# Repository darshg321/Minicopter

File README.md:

# Minicopter

A lightweight ESP-32 based drone capable of autonomous pathing, built for agility. Uses the GY-87 breakout board with a three-axis gyroscope + triaxial accelerometer + three-axis magnetic field + pressure. Charges a LiPo battery with USB-C and can be flashed with firmware.
Can be controlled with both pathing commands and bluetooth controls.

I made this project after getting inspiration from a different esp32 drone reel, and thought I could make that too
I've additionally always wanted to get into creating a from-scratch hardware project that includes microcontrollers and pcbs, and thought this was the perfect place to start

## Read the [JOURNAL.md](JOURNAL.md)

# BOM

| Value                               | Qty | Price (USD, approx) |
|-------------------------------------|-----|-------------|
| 10uF                                | 3   | 0.46        |
| 470pF                               | 1   | 0.4        |
| 2.2uF                               | 1   |    0.19         |
| 100nF                               | 2   |        0.14     |
| 10nF                                | 1   |         0.09    |
| 1uF                                 | 4   |          0.05   |
| SS34                                | 1   | 0.66        |
| LED                                 | 5   | 1.39        |
| 1N4148W                             | 4   | 0.77        |
| USB_C_Receptacle_USB2.0_16P         | 1   | 0.88        |
| Conn_01x02                          | 1   | 1.39        |
| Conn_01x02_Socket                   | 4   | 0.70        |
| AO3401A                             | 1   | 0.46        |
| 5.1K                                | 2   | 0.45        |
| 100K                                | 4   |     0.2        |
| 470                                 | 1   |       0.28      |
| 1.2K                                | 1   |          0.61   |
| 1K                                  | 4   |          0.2   |
| 10K                                 | 6   |            0.19 |
| SS-12D00                            | 1   | 1.39        |
| IRLML6344TRPBF                      | 4   | 1.08        |
| SPX3819M5-L-3-3                     | 1   | 0.46        |
| TP4056-42-ESOP8                     | 1   | 1.73        |
| ESP32-C3-WROOM-02                   | 1   | 3.28        |
| GY-87_Module                        | 1   | 3.00        |
| USBLC6-2P6                          | 1   | 0.46        |
| 3.7V 500mAh 902530 25C LiPo Battery | 3   | 12.68       |
| NewBeeDrone BDR Unicorn Edition Motors - 6mm Brushed Motors    | 1   | 19.99       |
| NewBeeDrone Venom V2 Super Durable Propellers     | 1   | 2.99        |
| Total (w/ shipping + tax)           |     | 138.15      |

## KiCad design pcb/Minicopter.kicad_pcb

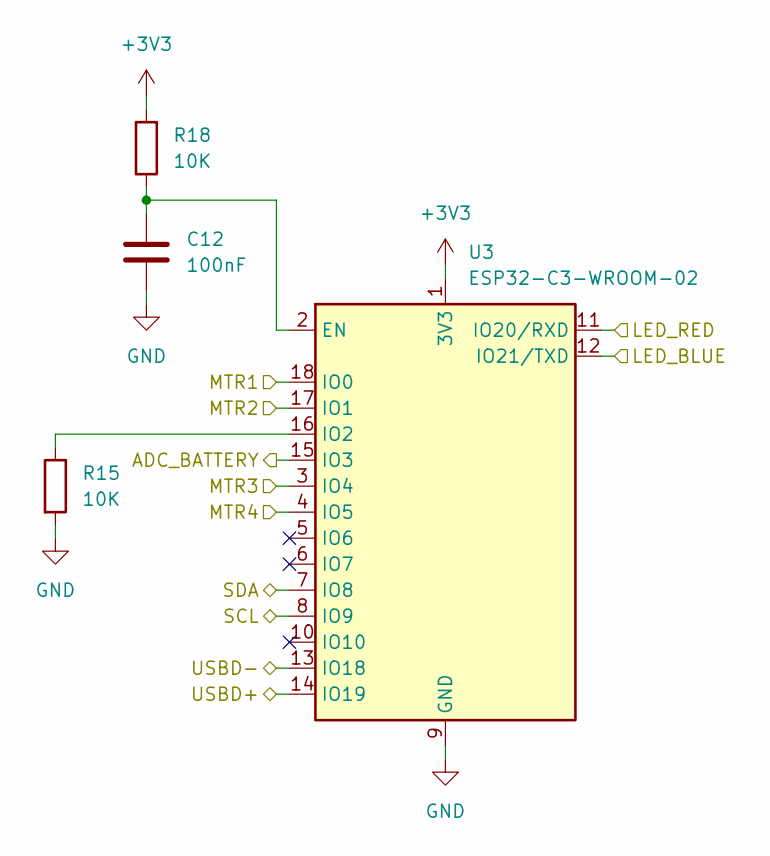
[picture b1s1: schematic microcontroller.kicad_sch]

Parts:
C12: 100nF; C_0603_1608Metric
R15, R18: 10K; R_0603_1608Metric
U3: ESP32-C3-WROOM-02

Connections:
+3V3: R18.2, U3.1 (3V3); also elsewhere on the board
/battery control/ADC_BATTERY: U3.15 (IO3); also elsewhere on the board
/microcontroller/LED_BLUE: U3.12 (IO21/TXD); also elsewhere on the board
/microcontroller/LED_RED: U3.11 (IO20/RXD); also elsewhere on the board
/microcontroller/MTR1: U3.18 (IO0); also elsewhere on the board
/microcontroller/MTR2: U3.17 (IO1); also elsewhere on the board
/microcontroller/MTR3: U3.3 (IO4); also elsewhere on the board
/microcontroller/MTR4: U3.4 (IO5); also elsewhere on the board
/microcontroller/SCL: U3.8 (IO9); also elsewhere on the board
/microcontroller/SDA: U3.7 (IO8); also elsewhere on the board
/microcontroller/USBD+: U3.14 (IO19); also elsewhere on the board
/microcontroller/USBD-: U3.13 (IO18); also elsewhere on the board
GND: C12.2, R15.2, U3.9 (GND), U3.19 (GND); also elsewhere on the board
unnamed: C12.1, R18.1, U3.2 (EN)
unnamed: R15.1, U3.16 (IO2)

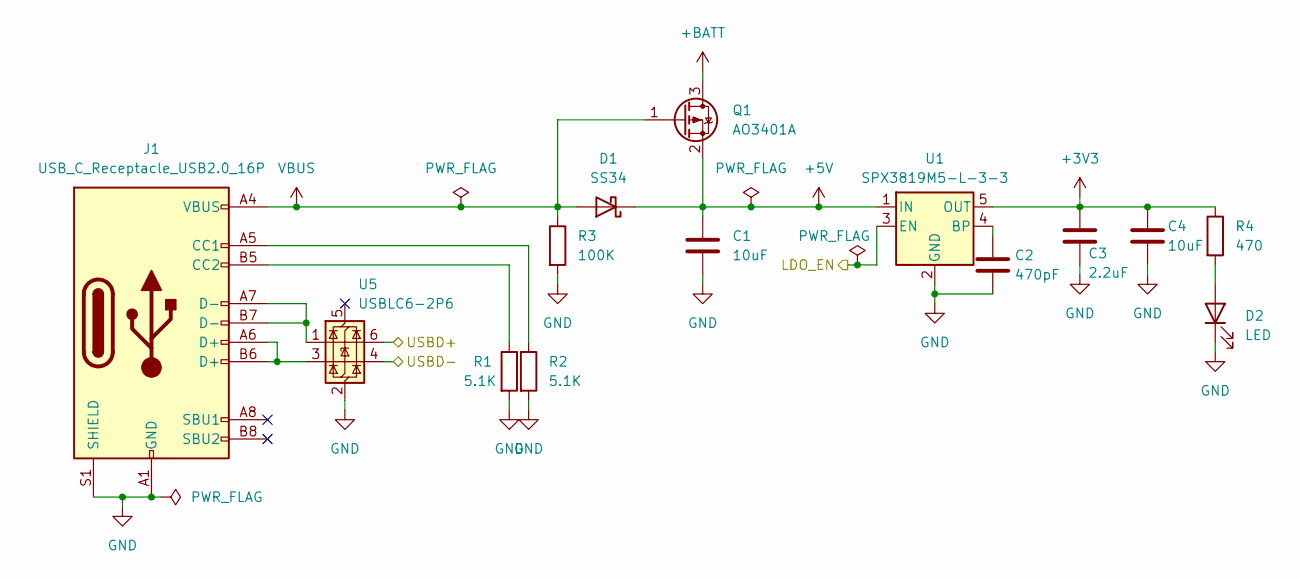
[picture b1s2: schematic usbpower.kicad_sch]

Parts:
C1, C4: 10uF; C_0603_1608Metric
C2: 470pF; C_0603_1608Metric
C3: 2.2uF; C_0603_1608Metric
D1: SS34; D_SMA
D2: LED; LED_0603_1608Metric
J1: USB_C_Receptacle_USB2.0_16P; USB_C_Receptacle_GCT_USB4085
Q1: AO3401A; SOT-23
R1, R2: 5.1K; R_0603_1608Metric
R3: 100K; R_0603_1608Metric
R4: 470; R_0603_1608Metric
U1: SPX3819M5-L-3-3; SOT-23-5
U5: USBLC6-2P6; SOT-666

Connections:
+3V3: C3.1, C4.1, R4.1, U1.5 (OUT); also elsewhere on the board
+5V: C1.1, D1.1 (K), Q1.2 (S), U1.1 (IN); also elsewhere on the board
+BATT: Q1.3 (D); also elsewhere on the board
/battery control/LDO_EN: U1.3 (EN); also elsewhere on the board
/microcontroller/USBD+: U5.6 (I/O1); also elsewhere on the board
/microcontroller/USBD-: U5.4 (I/O2); also elsewhere on the board
GND: C1.2, C2.2, C3.2, C4.2, D2.1 (K), J1.A1 (GND), J1.A12 (GND), J1.B1 (GND), J1.B12 (GND), J1.S1 (SHIELD), R1.2, R2.2, R3.2, U1.2 (GND), U5.2 (GND); also elsewhere on the board
unnamed: D2.2 (A), R4.2
unnamed: J1.A5 (CC1), R2.1
unnamed: J1.B5 (CC2), R1.1
unnamed: J1.A6 (D+), J1.B6 (D+), U5.3 (I/O2)
unnamed: J1.A7 (D-), J1.B7 (D-), U5.1 (I/O1)
unnamed: C2.1, U1.4 (BP)
VBUS: D1.2 (A), J1.A4 (VBUS), J1.A9 (VBUS), J1.B4 (VBUS), J1.B9 (VBUS), Q1.1 (G), R3.1; also elsewhere on the board

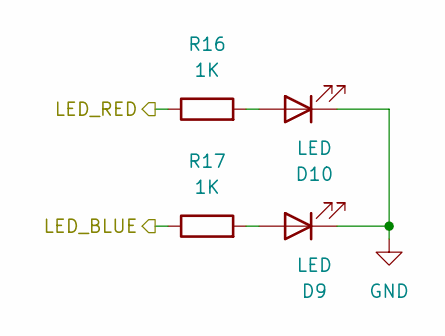
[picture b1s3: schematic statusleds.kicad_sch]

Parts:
D9, D10: LED; LED_0603_1608Metric
R16, R17: 1K; R_0603_1608Metric

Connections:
/microcontroller/LED_BLUE: R17.1; also elsewhere on the board
/microcontroller/LED_RED: R16.1; also elsewhere on the board
GND: D9.1 (K), D10.1 (K); also elsewhere on the board
unnamed: D9.2 (A), R17.2
unnamed: D10.2 (A), R16.2

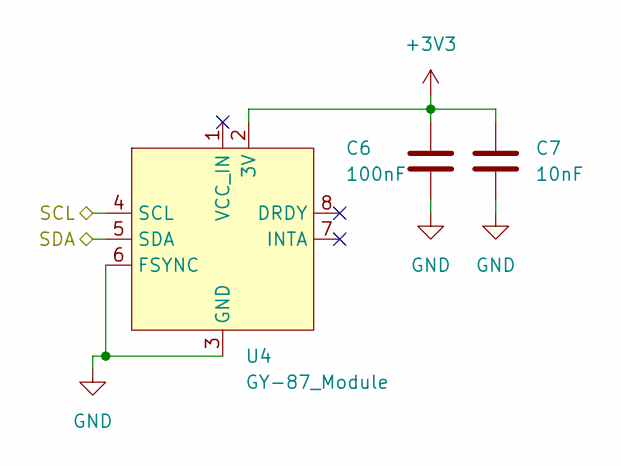
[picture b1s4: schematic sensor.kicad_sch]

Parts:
C6: 100nF; C_0603_1608Metric
C7: 10nF; C_0603_1608Metric
U4: GY-87_Module

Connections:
+3V3: C6.1, C7.1, U4.2 (3V); also elsewhere on the board
/microcontroller/SCL: U4.4 (SCL); also elsewhere on the board
/microcontroller/SDA: U4.5 (SDA); also elsewhere on the board
GND: C6.2, C7.2, U4.3 (GND), U4.6 (FSYNC); also elsewhere on the board

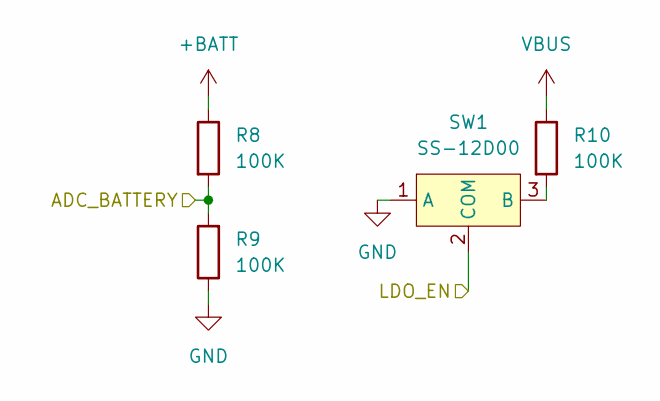
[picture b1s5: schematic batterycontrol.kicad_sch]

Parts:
R8, R9, R10: 100K; R_0603_1608Metric
SW1: SS-12D00; SS12-D00

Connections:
+BATT: R8.1; also elsewhere on the board
/battery control/ADC_BATTERY: R8.2, R9.2; also elsewhere on the board
/battery control/LDO_EN: SW1.2 (COM); also elsewhere on the board
GND: R9.1, SW1.1 (A); also elsewhere on the board
unnamed: R10.2, SW1.3 (B)
VBUS: R10.1; also elsewhere on the board

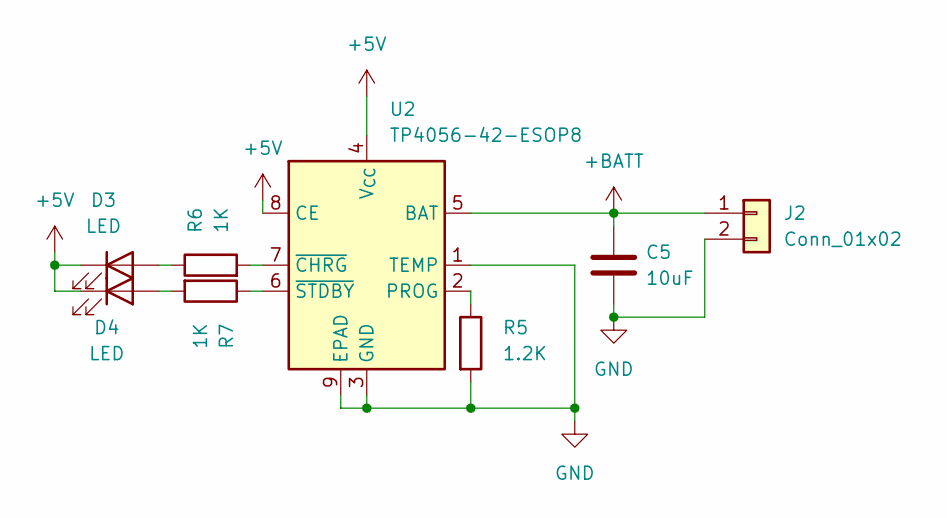
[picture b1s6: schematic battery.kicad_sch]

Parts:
C5: 10uF; C_0603_1608Metric
D3, D4: LED; LED_0603_1608Metric
J2: Conn_01x02; JST_PH_B2B-PH-SM4-TB_1x02-1MP_P2.00mm_Vertical
R5: 1.2K; R_0603_1608Metric
R6, R7: 1K; R_0603_1608Metric
U2: TP4056-42-ESOP8; SOIC-8-1EP_3.9x4.9mm_P1.27mm_EP2.41x3.3mm_ThermalVias

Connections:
+5V: D3.1 (K), D4.1 (K), U2.4 (V_{CC}), U2.8 (CE); also elsewhere on the board
+BATT: C5.1, J2.1, U2.5 (BAT); also elsewhere on the board
GND: C5.2, J2.2, R5.2, U2.1 (TEMP), U2.3 (GND), U2.9 (EPAD); also elsewhere on the board
unnamed: D3.2 (A), R6.1
unnamed: D4.2 (A), R7.2
unnamed: R5.1, U2.2 (PROG)
unnamed: R6.2, U2.7 (~CHRG)
unnamed: R7.1, U2.6 (~STDBY)

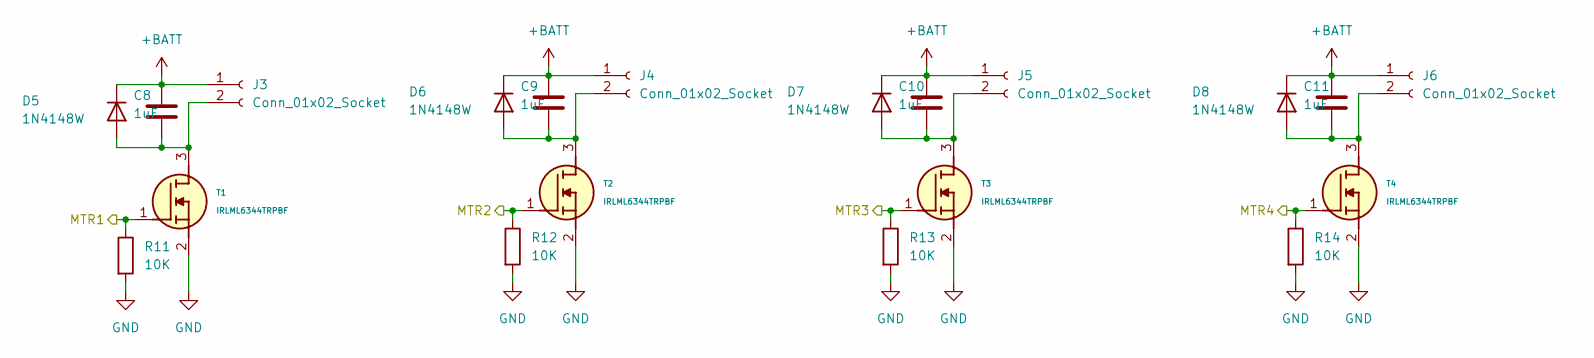
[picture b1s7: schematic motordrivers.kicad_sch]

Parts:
C8, C9, C10, C11: 1uF; C_0603_1608Metric
D5, D6, D7, D8: 1N4148W; D_SOD-123
J3, J4, J5, J6: Conn_01x02_Socket; JST_GH_BM02B-GHS-TBT_1x02-1MP_P1.25mm_Vertical
R11, R12, R13, R14: 10K; R_0603_1608Metric
T1, T2, T3, T4: IRLML6344TRPBF; MFR.Part # IRLML6344TRPBF-HXY; LCSC Part # C6285738

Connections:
+BATT: C8.1, C9.1, C10.1, C11.1, D5.1 (K), D6.1 (K), D7.1 (K), D8.1 (K), J3.1, J4.1, J5.1, J6.1; also elsewhere on the board
/microcontroller/MTR1: R11.1, T1.1 (G); also elsewhere on the board
/microcontroller/MTR2: R12.1, T2.1 (G); also elsewhere on the board
/microcontroller/MTR3: R13.1, T3.1 (G); also elsewhere on the board
/microcontroller/MTR4: R14.1, T4.1 (G); also elsewhere on the board
GND: R11.2, R12.2, R13.2, R14.2, T1.2 (S), T2.2 (S), T3.2 (S), T4.2 (S); also elsewhere on the board
unnamed: C8.2, D5.2 (A), J3.2, T1.3 (D)
unnamed: C9.2, D6.2 (A), J4.2, T2.3 (D)
unnamed: C10.2, D7.2 (A), J5.2, T3.3 (D)
unnamed: C11.2, D8.2 (A), J6.2, T4.3 (D)

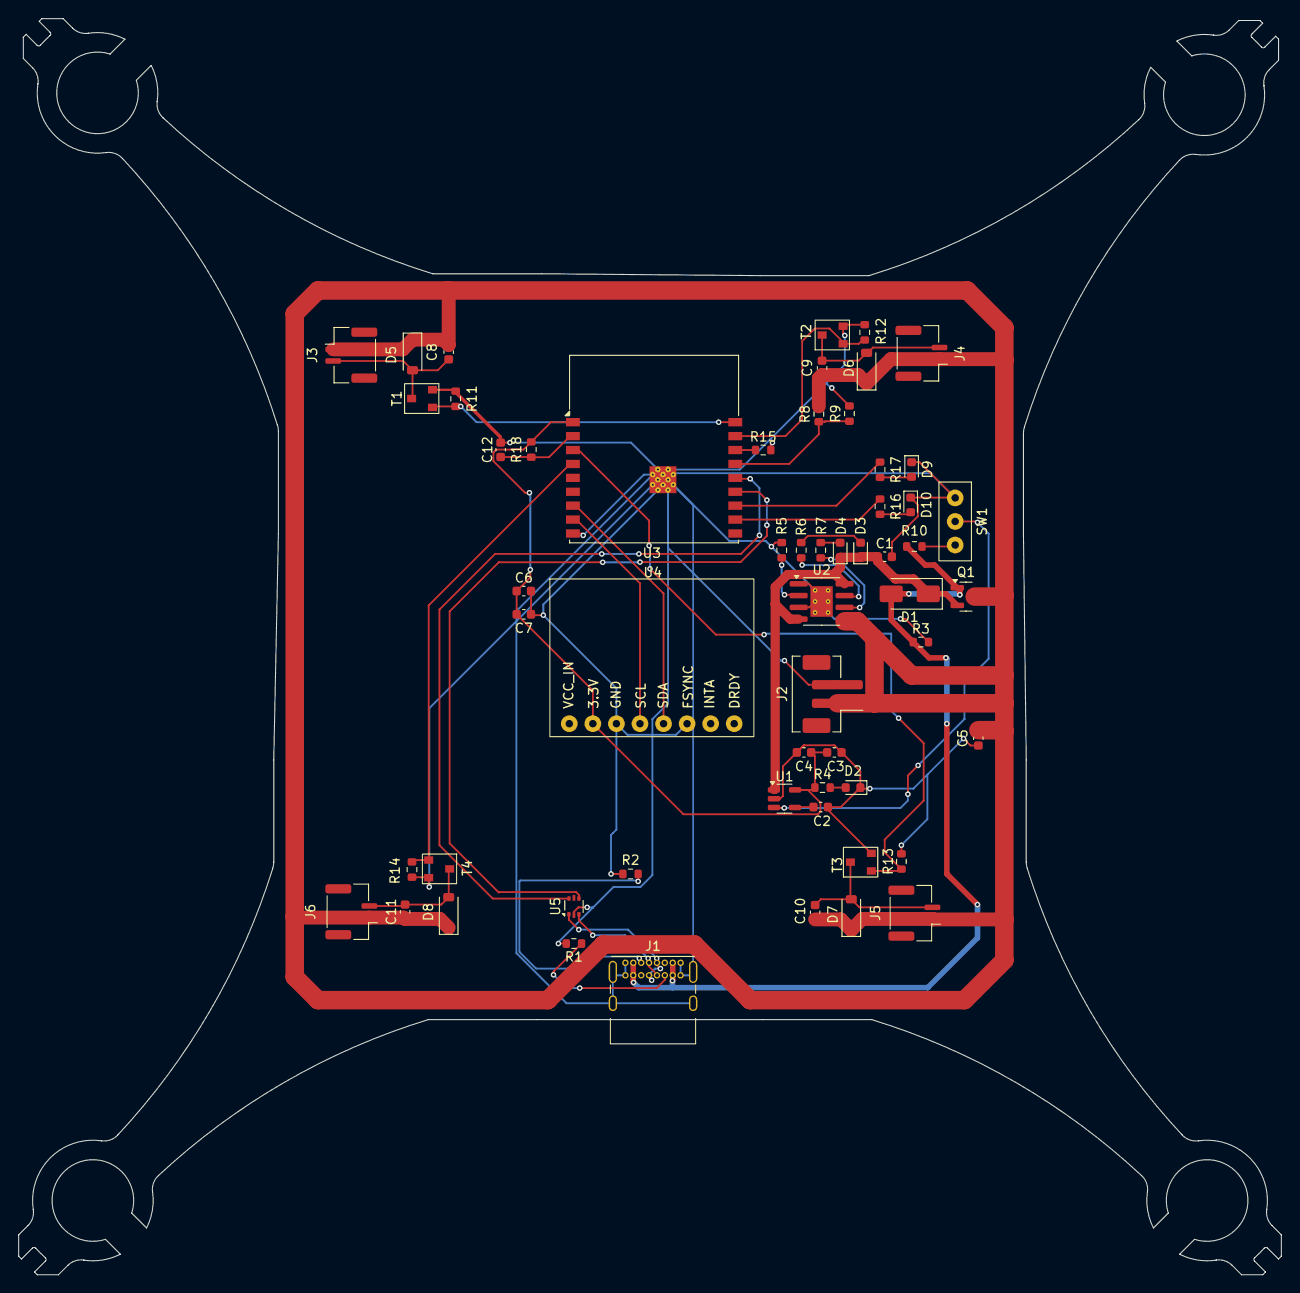
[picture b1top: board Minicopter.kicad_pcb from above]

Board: 2 copper layers, 136.1 x 135.4 mm, 57 parts (0 on the bottom side), 37 nets.

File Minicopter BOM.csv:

Reference,Value,Footprint,Qty,,Price (w/o shipping + taxes USD),,
"C1, C4, C5",10uF,Capacitor_SMD:C_0603_1608Metric,3,https://www.digikey.ca/en/products/detail/taiyo-yuden/LMK107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,0.46,,
C2,470pF,Capacitor_SMD:C_0603_1608Metric,1,https://www.digikey.ca/en/products/detail/kemet/C0603C471J5G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,0.4,,
C3,2.2uF,Capacitor_SMD:C_0603_1608Metric,1,https://www.digikey.ca/en/products/detail/taiyo-yuden/TMK107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,0.19,,
"C6, C12",100nF,Capacitor_SMD:C_0603_1608Metric,2,https://www.digikey.ca/en/products/detail/yageo/CC0603KRX7R7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,0.14,,
C7,10nF,Capacitor_SMD:C_0603_1608Metric,1,https://www.digikey.ca/en/products/detail/kemet/C0603C103K5R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,0.09,,
"C8, C9, C10, C11",1uF,Capacitor_SMD:C_0603_1608Metric,4,https://www.digikey.ca/en/products/detail/samsung-electro-me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,0.05,,
D1,SS34,Diode_SMD:D_SMA,1,https://www.digikey.ca/en/products/detail/onsemi/SS34/1052384,0.66,,
"D2, D3, D4, D9, D10",LED,LED_SMD:LED_0603_1608Metric,5,https://www.aliexpress.com/item/1005005431944057.html,1.39,,
"D5, D6, D7, D8",1N4148W,Diode_SMD:D_SOD-123,4,https://www.digikey.ca/en/products/detail/smc-diode-solution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,0.77,,
J1,USB_C_Receptacle_USB2.0_16P,Connector_USB:USB_C_Receptacle_GCT_USB4085,1,https://www.digikey.ca/en/products/detail/gct/USB4085-GF-A/98596622,0.88,,
J2,Conn_01x02,Connector_JST:JST_PH_B2B-PH-SM4-TB_1x02-1MP_P2.00mm_Vertical,1,https://www.aliexpress.com/item/1005008131930144.html,1.39,,
"J3, J4, J5, J6",Conn_01x02_Socket,Connector_JST:JST_GH_BM02B-GHS-TBT_1x02-1MP_P1.25mm_Vertical,4,https://www.aliexpress.com/item/1005005699355153.html,0.7,,
Q1,AO3401A,Package_TO_SOT_SMD:SOT-23,1,https://www.digikey.ca/en/products/detail/alpha-omega-semico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,0.46,,
"R1, R2",5.1K,Resistor_SMD:R_0603_1608Metric,2,https://www.digikey.ca/en/products/detail/yageo/RC0603FR-075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,0.45,,
"R3, R8, R9, R10",100K,Resistor_SMD:R_0603_1608Metric,4,https://www.digikey.ca/en/products/detail/stackpole-electron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,0.2,,
R4,470,Resistor_SMD:R_0603_1608Metric,1,https://www.digikey.ca/en/products/detail/te-connectivity-pa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,0.28,,
R5,1.2K,Resistor_SMD:R_0603_1608Metric,1,https://www.digikey.ca/en/products/detail/panasonic-electron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,0.61,,
"R6, R7, R16, R17",1K,Resistor_SMD:R_0603_1608Metric,4,https://www.digikey.ca/en/products/detail/stackpole-electron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,0.2,,
"R11–R15, R18",10K,Resistor_SMD:R_0603_1608Metric,6,https://www.digikey.ca/en/products/detail/stackpole-electron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,0.19,,
SW1,SS-12D00,SS-12D00:SS12-D00,1,https://www.aliexpress.com/item/4001187999740.htmll,1.39,,
"T1, T2, T3, T4",IRLML6344TRPBF,IRLML6344TRPBF:IRLML6344TRPBF,4,https://www.aliexpress.com/item/1005005586173911.html,1.08,,
U1,SPX3819M5-L-3-3,Package_TO_SOT_SMD:SOT-23-5,1,https://www.digikey.ca/en/products/detail/maxlinear-inc/SPX3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,0.46,,
U2,TP4056-42-ESOP8,Package_SO:SOIC-8-1EP_3.9x4.9mm_P1.27mm_EP2.41x3.3mm_ThermalVias,1,https://www.aliexpress.com/item/1005009057944694.html,1.73,,
U3,ESP32-C3-WROOM-02,RF_Module:ESP32-C3-WROOM-02,1,https://www.digikey.ca/en/products/detail/espressif-systems/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,3.28,,
U4,GY-87_Module,GY-87_Module:GY-87_Module,1,https://www.aliexpress.com/i/32668253323.html,3,,Total (USD)
U5,USBLC6-2P6,Package_TO_SOT_SMD:SOT-666,1,https://www.digikey.ca/en/products/detail/stmicroelectronics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,0.46,Subtotal,58.21
,2.54mm Headers,,1,https://www.digikey.ca/en/products/detail/amphenol-cs-fci/10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,1.64,NewBeeDrone,24.17
,3.7V 500mAh 902530 25C LiPo Battery,,3,https://www.aliexpress.com/item/1005007016796736.html,12.68,Digikey,20
,NewBeeDrone BDR Unicorn Edition Motors - 6mm Brushed Motors ,,1,https://newbeedrone.com/collections/drone-motors/products/ne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,19.99,Aliexpress,25.77
,NewBeeDrone Venom V2 Super Durable Propellers 31mm -0.8mm Shaft ,,1,https://newbeedrone.com/collections/drone-propellers/product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,2.99,Taxes,10
,,,,,,,
,,,,,58.21,,138.15

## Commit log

2025-07-08 power schem
2025-07-09 battery
2025-07-09 with errors
2025-07-09 finished schematic
2025-07-10 schematic done
2025-07-16 without gnd
2025-07-16 donedone
2025-07-18 done hopefully
2025-07-18 oops now done hopefully
2025-07-22 update bom
2025-07-25 update bom:
2025-07-27 price went up :pensive:
2025-07-27 Revert "price went up :pensive:"
    This reverts commit 4fa7545903ad4b724715b33760c9a4a9f241c5e7.
2025-07-28 added pathing
2025-07-29 fixed usb placement
2025-08-01 render
2025-08-15 assembly progress
